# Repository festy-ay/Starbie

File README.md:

# Starbie

A star-shaped ESP32-C3 PCB with an OLED display, an MPU6050 motion sensor and a DHT11 sensor.

## Credits
This project is based on the Starbie guide by SharKing Studios:
https://github.com/SharKingStudios/Starbie

## What I changed
- Added a battery connector and a slide switch
- Added a second reset button
- Added mounting holes
- Added silkscreen artwork (starfish and waves) and a "Starbie" label

## What's in this repo
- KiCad files (.kicad_pro, .kicad_sch, .kicad_pcb)
- gerbers/ (manufacturing files)
- Imported Libraries (XIAO ESP32 Lbraries and co.)
- BOM.csv (parts list)

## License
The original design belongs to its authors and is covered by its own license: https://github.com/SharKingStudios/Starbie/blob/main/LICENSE

##
The starfish designs were downloaded form online platforms and converted using Inkscape then imported into the project. The dowloaded art files (.png) and converted files (.svg) are not provided here but you can make your's and import it into the project!.

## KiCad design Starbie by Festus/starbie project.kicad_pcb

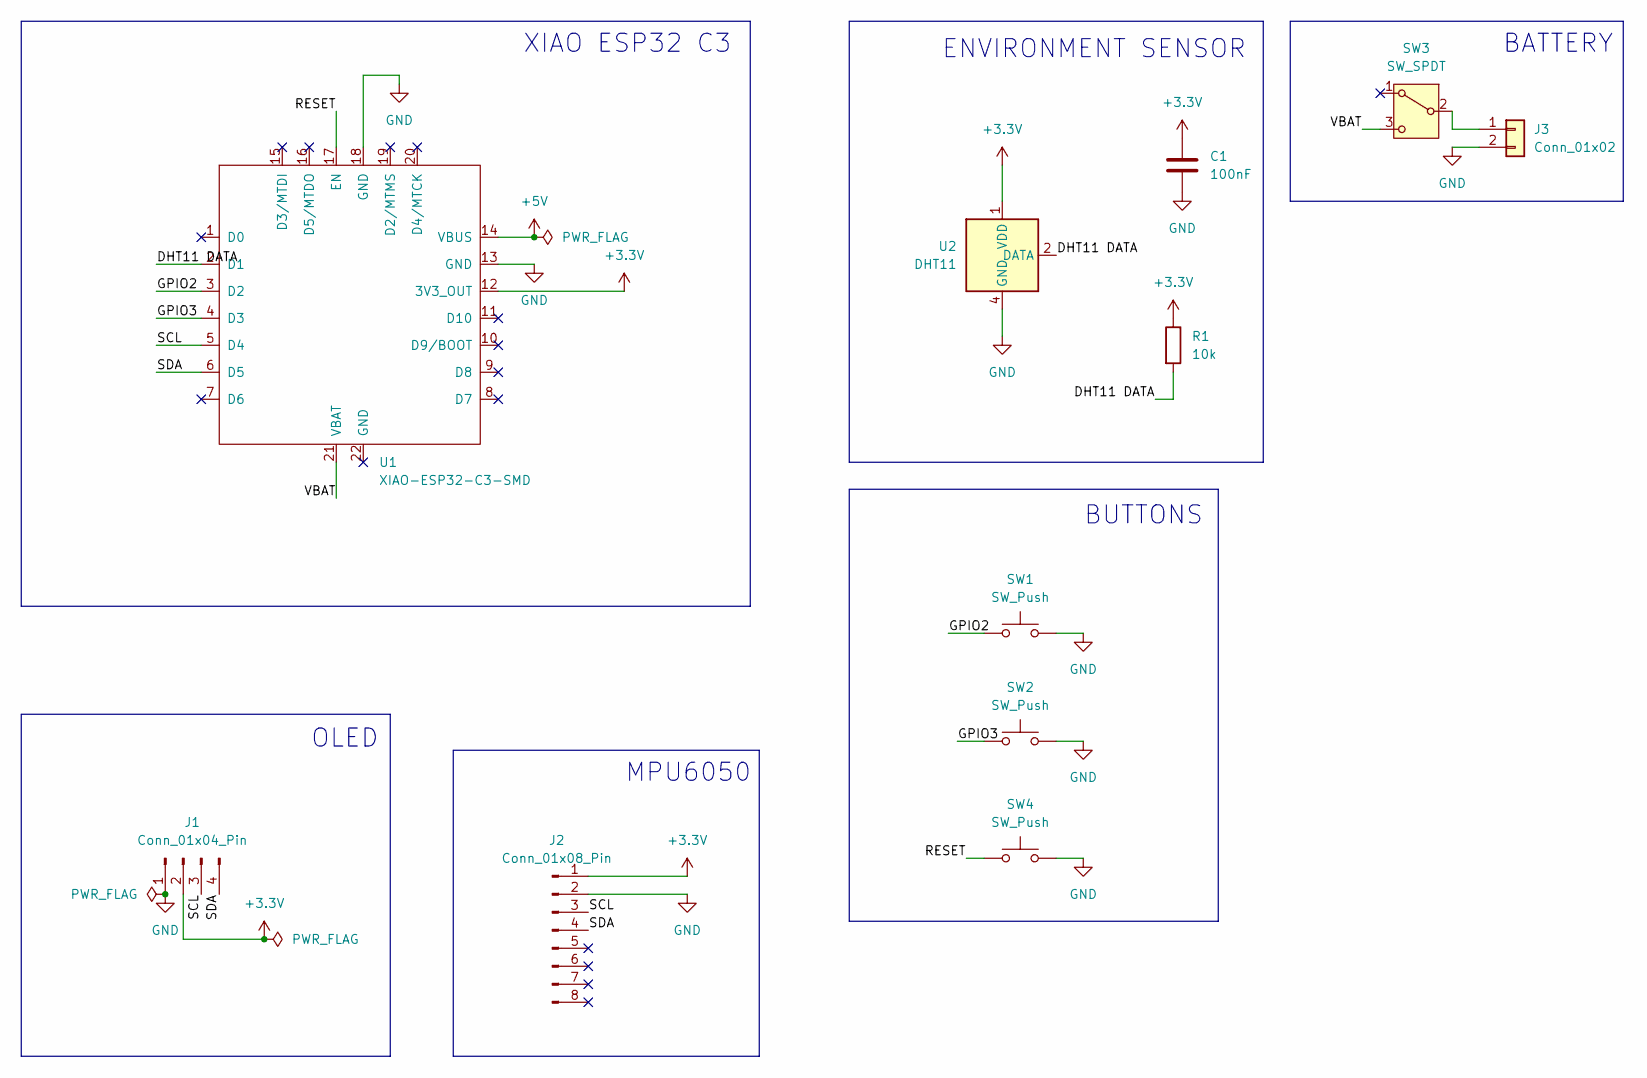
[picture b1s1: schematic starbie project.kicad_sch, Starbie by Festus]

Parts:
C1: 100nF; C_0603_1608Metric
J1: Conn_01x04_Pin; Display_128x64_096_I2C
J2: Conn_01x08_Pin; PinHeader_1x08_P2.54mm_Vertical
J3: Conn_01x02; JST_PH_B2B-PH-K_1x02_P2.00mm_Vertical
R1: 10k; R_Axial_DIN0204_L3.6mm_D1.6mm_P7.62mm_Horizontal
SW1, SW2, SW4: SW_Push; SW_Cherry_MX_1.00u_PCB
SW3: SW_SPDT; SW_SPDT_Shouhan_MSK12C02
U1: XIAO-ESP32-C3-SMD
U2: DHT11; Aosong_DHT11_5.5x12.0_P2.54mm

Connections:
+3.3V: C1.1, J1.2, J2.1, R1.1, U1.12 (3V3_OUT), U2.1 (VDD)
+5V: U1.14 (VBUS)
/DHT11 DATA: R1.2, U1.2 (D1), U2.2 (DATA)
/GPIO2: SW1.1, U1.3 (D2)
/GPIO3: SW2.1, U1.4 (D3)
/RESET: SW4.1, U1.17 (EN)
/SCL: J1.3, J2.3, U1.5 (D4)
/SDA: J1.4, J2.4, U1.6 (D5)
/VBAT: SW3.3 (C), U1.21 (VBAT)
GND: C1.2, J1.1, J2.2, J3.2, SW1.2, SW2.2, SW4.2, U1.13 (GND), U1.18 (GND), U2.4 (GND)
unnamed: J3.1, SW3.2 (B)

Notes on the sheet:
BUTTONS
MPU6050
OLED
XIAO ESP32 C3
BATTERY
ENVIRONMENT SENSOR

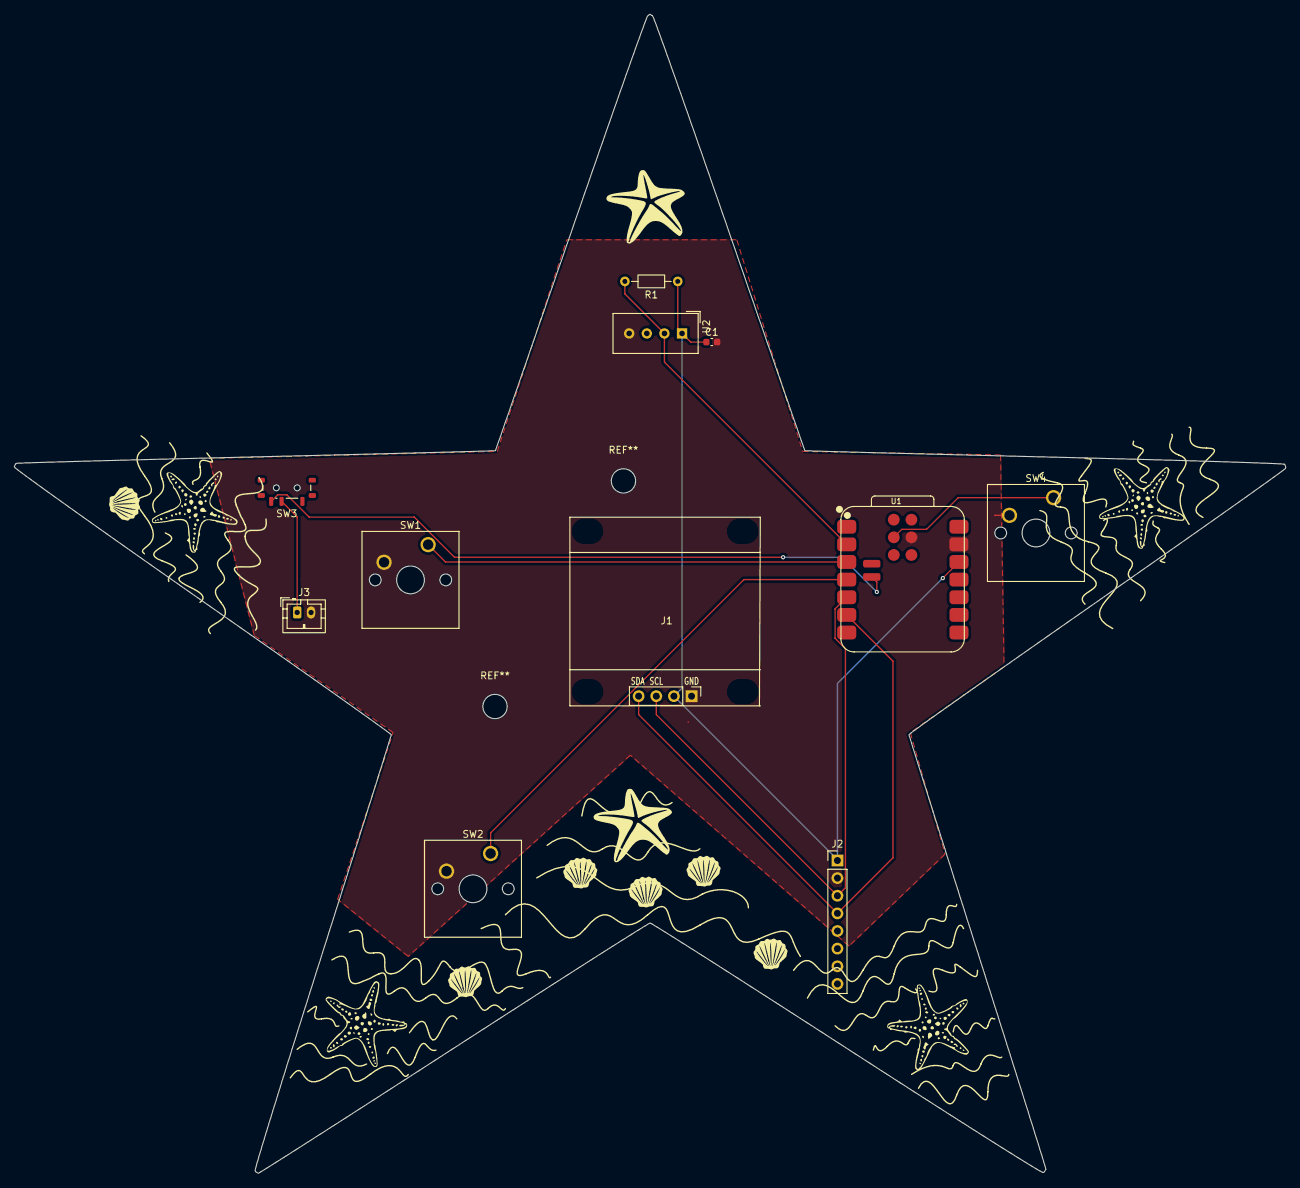
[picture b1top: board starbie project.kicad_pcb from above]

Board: 2 copper layers, 183.2 x 167.0 mm, 11 parts (0 on the bottom side), 10 nets.
